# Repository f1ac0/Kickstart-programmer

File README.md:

# Kickstart programmer
Program a 512KB 27C400, 1MB 27C800, 2MB 27C160 or 4MB 27C322 EPROM chip with a programmer that supports 27C4096@DIP40 devices, like the TL866 and clones.

These chips are used in Amiga computers, either directly with a single kickstart image (512K or 1MB ones), or with a kickstart selector and multiple images inside a single chip.

# Disclaimer
This is a hobbyist project, it comes with no warranty and no support.

I publish this work using the CC-BY-NC-SA license.

If you find it useful and want to reward me : I am always looking for Amiga/Amstrad CPC hardware to repair and hack, please contact me.

# Making it
Check for shorts at least between 5V and GND traces before applying power !

- You may leave Q1, R3, R4 and R5 unpopulated if you do not plan to use 27C322 devices. In this case, replace the switch with bridges between pins 2-3 and 5-6.
- First solder SMD parts then the pin header to the programmer. Solder the socket last, since it will block access to some pins from the top of the board. You may use a ZIF socket, or two shorter/cut sockets since 42 pins ones are hard to find nowadays.

# Using it
1. Place EPROM in lowest position in the socket.
2. Set the slide switch for the device to be programmed.
3. Set the jumpers for the 512KB bank to access:
    400: none,  800: A18,  160: A18-19,  322: A18-19-20
4. On TL866, select 27C4096@DIP40

To prepare the ROM image(s) containing your kickstarts
- Choose your kickstart size, 512KB or 1MB : all kickstarts on the same rom must have the same size for the selector to work correctly
- 1MB images are convenient for recent systems. They come in two parts : the extended part need to be placed first (A18=0), then the standard part (A18=1).
- LOW byte and HIGH byte are swapped. Kickstart ROM images used by UAE are not swapped however, so you need to convert them if you plan to test them before programming. Use `dd if=source of=destination conv=swab` or `srec_cat source -binary -byte-swap 2 -o destination -binary`.
- Some 32bits systems use two physical ROM chips : it is necessary to split the image between low and high 16bit words : `srec_cat source -binary -split 4 0 2 -o destination12 -binary` (LOW, U6A ?) and `srec_cat source -binary -split 4 2 2 -o destination34 -binary` (HIGH, U6B ?)
- You may swap bytes and split words at the same time : `srec_cat source -binary -split 4 0 2 -byte-swap 2 -o destination12 -binary` and `srec_cat source -binary -split 4 2 2 -byte-swap 2 -o destination34 -binary`

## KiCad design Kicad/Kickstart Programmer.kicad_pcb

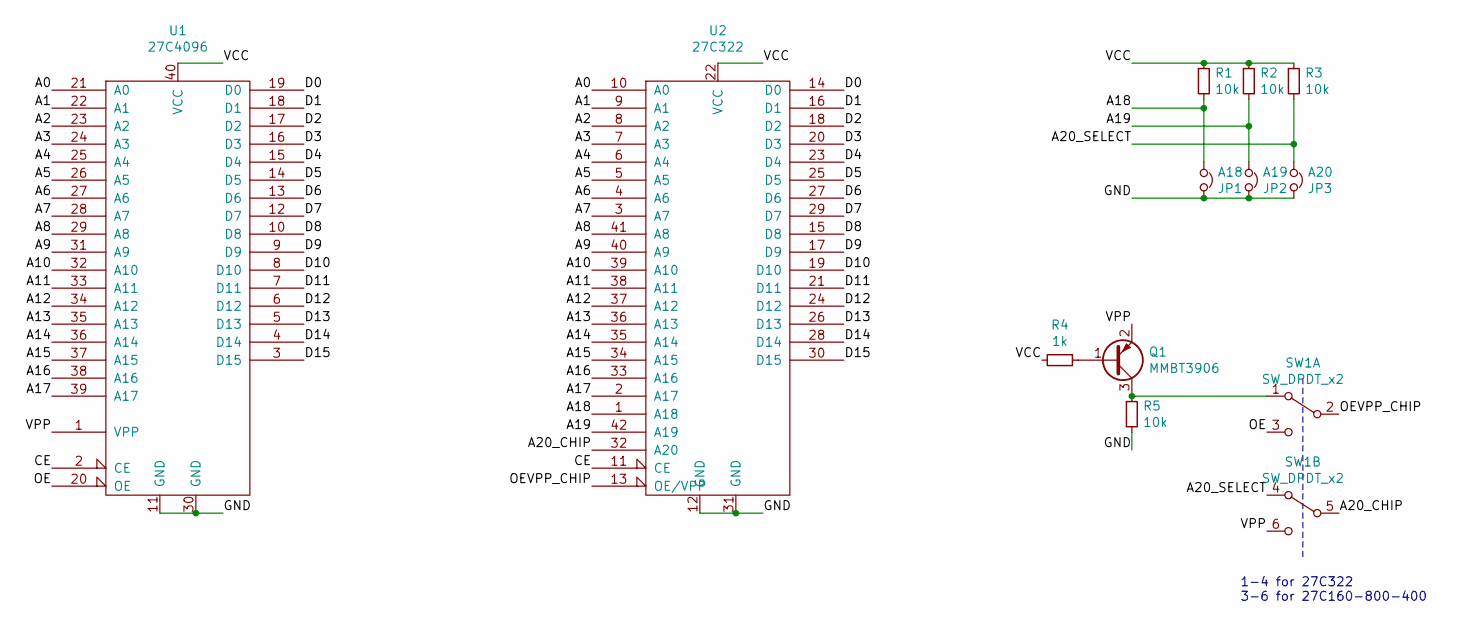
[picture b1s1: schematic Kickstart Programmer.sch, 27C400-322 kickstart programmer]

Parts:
JP1: A18; Pin_Header_1x2_EdgeMount_Pitch2.54mm
JP2: A19; Pin_Header_1x2_EdgeMount_Pitch2.54mm
JP3: A20; Pin_Header_1x2_EdgeMount_Pitch2.54mm
Q1: MMBT3906; SOT-23_Handsoldering
R1, R2, R3, R5: 10k; R_0805_HandSoldering
R4: 1k; R_0805_HandSoldering
SW1: SW_DPDT_x2; SW_DPDT_Edgemount
U1: 27C4096; DIP-40_W15.24mm
U2: 27C322; DIP-42_W15.24mm_Socket_largeholes

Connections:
/A0: U1.21 (A0), U2.10 (A0)
/A1: U1.22 (A1), U2.9 (A1)
/A2: U1.23 (A2), U2.8 (A2)
/A3: U1.24 (A3), U2.7 (A3)
/A4: U1.25 (A4), U2.6 (A4)
/A5: U1.26 (A5), U2.5 (A5)
/A6: U1.27 (A6), U2.4 (A6)
/A7: U1.28 (A7), U2.3 (A7)
/A8: U1.29 (A8), U2.41 (A8)
/A9: U1.31 (A9), U2.40 (A9)
/A10: U1.32 (A10), U2.39 (A10)
/A11: U1.33 (A11), U2.38 (A11)
/A12: U1.34 (A12), U2.37 (A12)
/A13: U1.35 (A13), U2.36 (A13)
/A14: U1.36 (A14), U2.35 (A14)
/A15: U1.37 (A15), U2.34 (A15)
/A16: U1.38 (A16), U2.33 (A16)
/A17: U1.39 (A17), U2.2 (A17)
/A18: JP1.2, R1.2, U2.1 (A18)
/A19: JP2.2, R2.2, U2.42 (A19)
/A20_CHIP: SW1.5 (B), U2.32 (A20)
/A20_SELECT: JP3.2, R3.2, SW1.4 (A)
/CE: U1.2 (CE), U2.11 (CE)
/D0: U1.19 (D0), U2.14 (D0)
/D1: U1.18 (D1), U2.16 (D1)
/D2: U1.17 (D2), U2.18 (D2)
/D3: U1.16 (D3), U2.20 (D3)
/D4: U1.15 (D4), U2.23 (D4)
/D5: U1.14 (D5), U2.25 (D5)
/D6: U1.13 (D6), U2.27 (D6)
/D7: U1.12 (D7), U2.29 (D7)
/D8: U1.10 (D8), U2.15 (D8)
/D9: U1.9 (D9), U2.17 (D9)
/D10: U1.8 (D10), U2.19 (D10)
/D11: U1.7 (D11), U2.21 (D11)
/D12: U1.6 (D12), U2.24 (D12)
/D13: U1.5 (D13), U2.26 (D13)
/D14: U1.4 (D14), U2.28 (D14)
/D15: U1.3 (D15), U2.30 (D15)
/GND: JP1.1, JP2.1, JP3.1, R5.2, U1.11 (GND), U1.30 (GND), U2.12 (GND), U2.31 (GND)
/OE: SW1.3 (C), U1.20 (OE)
/OEVPP_CHIP: SW1.2 (B), U2.13 (OE/VPP)
/VCC: R1.1, R2.1, R3.1, R4.2, U1.40 (VCC), U2.22 (VCC)
/VPP: Q1.2 (E), SW1.6 (C), U1.1 (VPP)
unnamed: Q1.1 (B), R4.1
unnamed: Q1.3 (C), R5.1, SW1.1 (A)

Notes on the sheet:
1-4 for 27C322 3-6 for 27C160-800-400

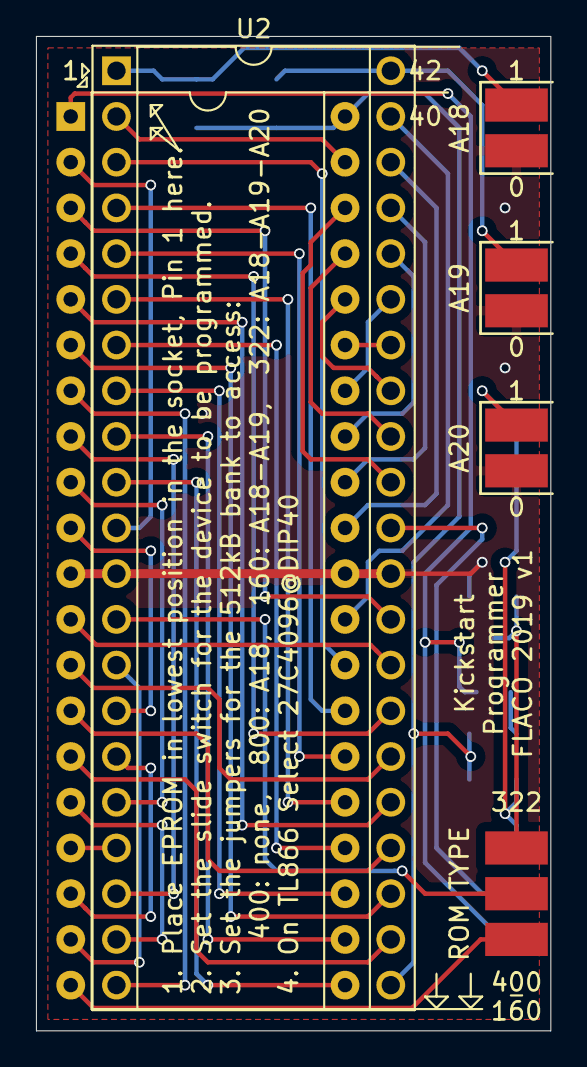
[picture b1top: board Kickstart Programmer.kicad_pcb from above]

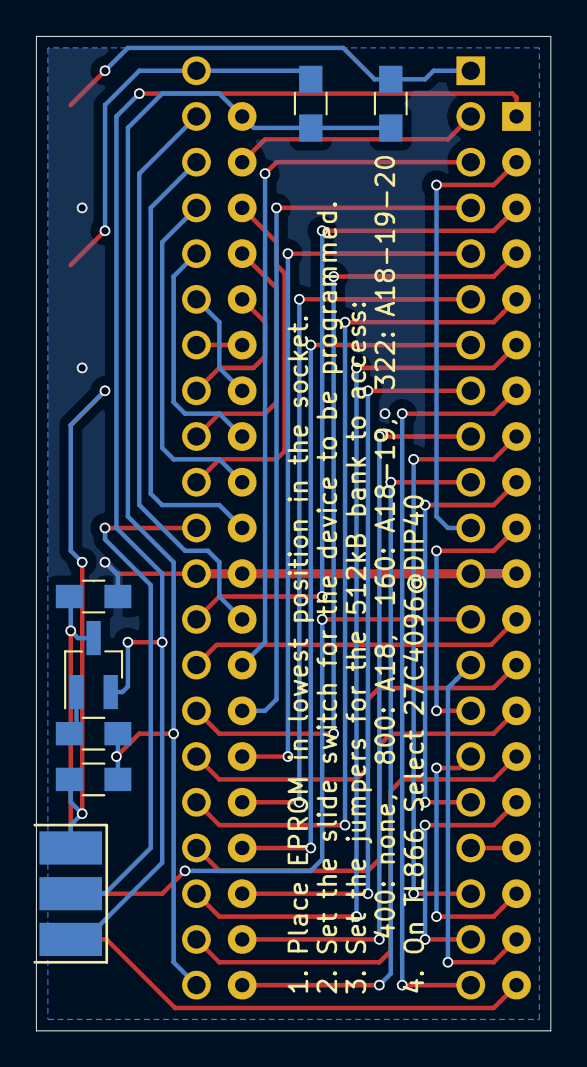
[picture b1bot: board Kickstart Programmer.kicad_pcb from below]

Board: 2 copper layers, 28.6 x 55.2 mm, 12 parts (7 on the bottom side), 46 nets.

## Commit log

2020-09-08 Repository init with KiCAD files, Readme and License
2022-02-15 Photo and InteractiveHtmlBom

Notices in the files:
Kicad/Kickstart Programmer.kicad_pcb:
FLACO 2019, licence of this PCB is CC-BY-NC-SA
Kicad/Kickstart Programmer.sch:
FLACO 2019, licence of this schematic is CC-BY-NC-SA
